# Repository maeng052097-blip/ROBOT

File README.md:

# Recycling Waste Detection Robot

재활용 쓰레기를 자동으로 인식하고 분류하는 자율주행 로봇 프로젝트

## 프로젝트 개요

카메라와 LiDAR를 활용하여 재활용 쓰레기(비닐, 스티로폼, 유리병, 종이류, 캔류, 페트병, 플라스틱류)를 실시간으로 인식하고, 물체까지의 거리를 측정하는 시스템입니다.

최종 목표는 노트북(HP VICTUS 15, RTX 4060)에서 직접 실행하여 자율주행 로봇으로 운용하는 것입니다.

## 시스템 구성

| 장비 | 용도 |
|------|------|
| HP VICTUS 15 (RTX 4060, 8GB VRAM) | 모델 학습·검증 + 실행(최종 배포 타겟) |
| Logitech StreamCam x2 | 물체 인식 카메라 |
| YDLIDAR X2 | 2D 거리 측정 (360°, 8m) |

## 인식 가능한 쓰레기 분류 (7개 클래스)

| 클래스 | 영문명 | 학습 데이터 |
|--------|--------|-----------|
| 비닐 | vinyl | 800장 |
| 스티로폼 | styrofoam | 800장 |
| 유리병 | glass_bottle | 800장 |
| 종이류 | paper | 800장 |
| 캔류 | can | 800장 |
| 페트병 | pet_bottle | 800장 |
| 플라스틱류 | plastic | 800장 |

## 학습 결과

- **모델:** YOLOv8n (nano)
- **데이터:** AIHUB 생활 폐기물 이미지 5,600장 (train 4,480 / val 1,120)
- **학습 환경:** NVIDIA RTX 4060 Laptop GPU (8GB VRAM)

| 지표 | 값 |
|------|-----|
| mAP@0.5 | 0.756 |
| mAP@0.5:0.95 | 0.665 |
| 추론 속도 (GPU) | 1.3ms/장 |

### 클래스별 성능 (AP@0.5)

| 클래스 | AP |
|--------|------|
| 스티로폼 | 0.923 |
| 캔류 | 0.759 |
| 비닐 | 0.759 |
| 페트병 | 0.745 |
| 종이류 | 0.739 |
| 플라스틱류 | 0.707 |
| 유리병 | 0.658 |

## 프로젝트 구조

```
ddd/
├── common/                      # 공용 모듈
│   ├── config.py                #   포트·임계값·경로 중앙 설정
│   ├── classes.py               #   재활용 7개 클래스 정의
│   ├── safety.py                #   LiDAR 전방 안전판단(SAFE/SLOW/DANGER)
│   ├── fusion.py                #   카메라 베어링 + LiDAR 거리 융합
│   └── camera.py                #   카메라 빠른 열기(DSHOW) + 16:9
├── config/
│   └── data.yaml                # YOLO 학습 설정
├── data/scripts/                # 데이터 변환·검증
│   ├── convert_aihub_to_yolo_v3.py
│   └── verify_labels.py
├── drivers/
│   └── LidarX2.py               # YDLIDAR X2 드라이버
├── inference/
│   └── detector.py              # YOLO 목표 탐지(좌/중/우 방향)
├── models/weights/best.pt       # 학습 가중치 (직접 배치, git 제외)
├── tests/                       # 하드웨어 스모크 테스트 + 단위 테스트
│   ├── check_devices.py         #   Arduino/LiDAR/웹캠 연결 점검
│   ├── find_camera.py           #   카메라 인덱스 찾기(내장캠 vs Logitech)
│   ├── find_front.py            #   전방각(FORWARD_ANGLE_DEG) 찾기
│   ├── test_scan.py             #   LiDAR 전방거리·안전상태(텍스트)
│   ├── test_lidar_parser.py     #   LiDAR 패킷 파서 단위테스트(HW 불필요)
│   ├── test_fusion.py           #   카메라+LiDAR 물체거리 융합 테스트
│   └── webcam_test.py           #   웹캠 + YOLO 탐지
├── visualization/
│   ├── realtime_radar.py        #   LiDAR 실시간 레이더(극좌표) 시각화
│   └── realtime_view.py         #   카메라 + LiDAR 통합 뷰
├── urt/                         # 통합 주행 + 모터
│   ├── 웹캠_LiDAR_주행제어.py     #   통합 주행 컨트롤러
│   ├── 모터2개_시리얼테스트.py    #   모터 수동 테스트(w/a/d/s)
│   ├── motor_serial.py          #   시리얼 전송 헬퍼
│   └── arduino_motor/           #   Arduino 펌웨어(PlatformIO)
└── requirements.txt
```

## 설치 및 실행

### 1. 환경 설정

```bash
# Python 3.13 가상환경 생성
python -m venv recycling_env

# 활성화 (Windows)
recycling_env\Scripts\activate

# PyTorch 설치 (CUDA 12.x)
pip install torch torchvision torchaudio --index-url https://download.pytorch.org/whl/cu124

# 나머지 패키지
pip install -r requirements.txt
```

### 2. 데이터 변환 (AIHUB → YOLO)

```bash
# AIHUB 생활 폐기물 이미지 데이터셋 필요
# https://aihub.or.kr/ (dataSetSn=140)
python data/scripts/convert_aihub_to_yolo_v3.py
```

### 3. 모델 학습

```bash
python -c "
from ultralytics import YOLO
model = YOLO('yolov8n.pt')
model.train(data='config/data.yaml', epochs=100, imgsz=640, batch=16, device=0)
"
```

### 4. LiDAR 테스트

```bash
python tests/test_scan.py
```

### 5. 하드웨어 브링업 / 통합 주행

VSCode 에서 `ddd` 폴더를 열면 Run and Debug(F5) 에 실행 구성이 준비돼 있다. 터미널로도 가능:

```bash
python tests/check_devices.py        # Arduino/LiDAR/웹캠 연결 점검
python urt/모터2개_시리얼테스트.py    # 모터 2개 수동 구동 (w/a/d/s)
python tests/webcam_test.py          # 웹캠 + YOLO 탐지/방향
python urt/웹캠_LiDAR_주행제어.py     # 통합 주행 (웹캠+LiDAR+Arduino)
```

- 학습 가중치 `best.pt` 는 `models/weights/best.pt` 에 둔다(git 제외).
- 포트/임계값은 `common/config.py` 에서 관리. LiDAR 없이 시험하려면 `REQUIRE_LIDAR=False`.
- Arduino 펌웨어는 PlatformIO 로 `urt/arduino_motor` 를 업로드.

## 진행 상황

- [x] 하드웨어 개별 테스트 (카메라, LiDAR, 모터)
- [x] 개발 환경 구축 (PyTorch + CUDA)
- [x] AIHUB 데이터 → YOLO 변환 / YOLOv8n 학습 (mAP@0.5 = 0.756)
- [x] 코드 통합: 공통 설정 · LiDAR 드라이버 · YOLO 탐지 · 모터 제어 연결
- [x] 통합 주행 컨트롤러 (웹캠 방향 + LiDAR 안전 SAFE/SLOW/DANGER + Arduino)
- [x] 하드웨어 브링업 스모크 테스트 (장치점검 / LiDAR / 웹캠)
- [ ] 실하드웨어 통합 주행 검증 및 임계값 튜닝
- [ ] 추가 데이터로 재학습 (정확도 향상)
- [ ] 노트북 실시간 추론 최적화 (TensorRT/FP16, 선택)

## 데이터셋 출처

- [AIHUB 생활 폐기물 이미지](https://aihub.or.kr/aihubdata/data/view.do?currMenu=115&topMenu=100&dataSetSn=140)
- 라벨과 이미지 배치 불일치로 인해 ZIP 카테고리 기반 자동 바운딩박스 생성 방식 사용

## 기술 스택

- **물체 인식:** YOLOv8 (ultralytics)
- **거리 측정:** YDLIDAR X2 (커스텀 드라이버)
- **카메라:** OpenCV + Logitech StreamCam
- **학습 GPU:** NVIDIA RTX 4060 Laptop (8GB VRAM)
- **실행 환경:** 노트북 (HP VICTUS 15, RTX 4060) — ultralytics + CUDA 직접 실행

## 라이선스

MIT License

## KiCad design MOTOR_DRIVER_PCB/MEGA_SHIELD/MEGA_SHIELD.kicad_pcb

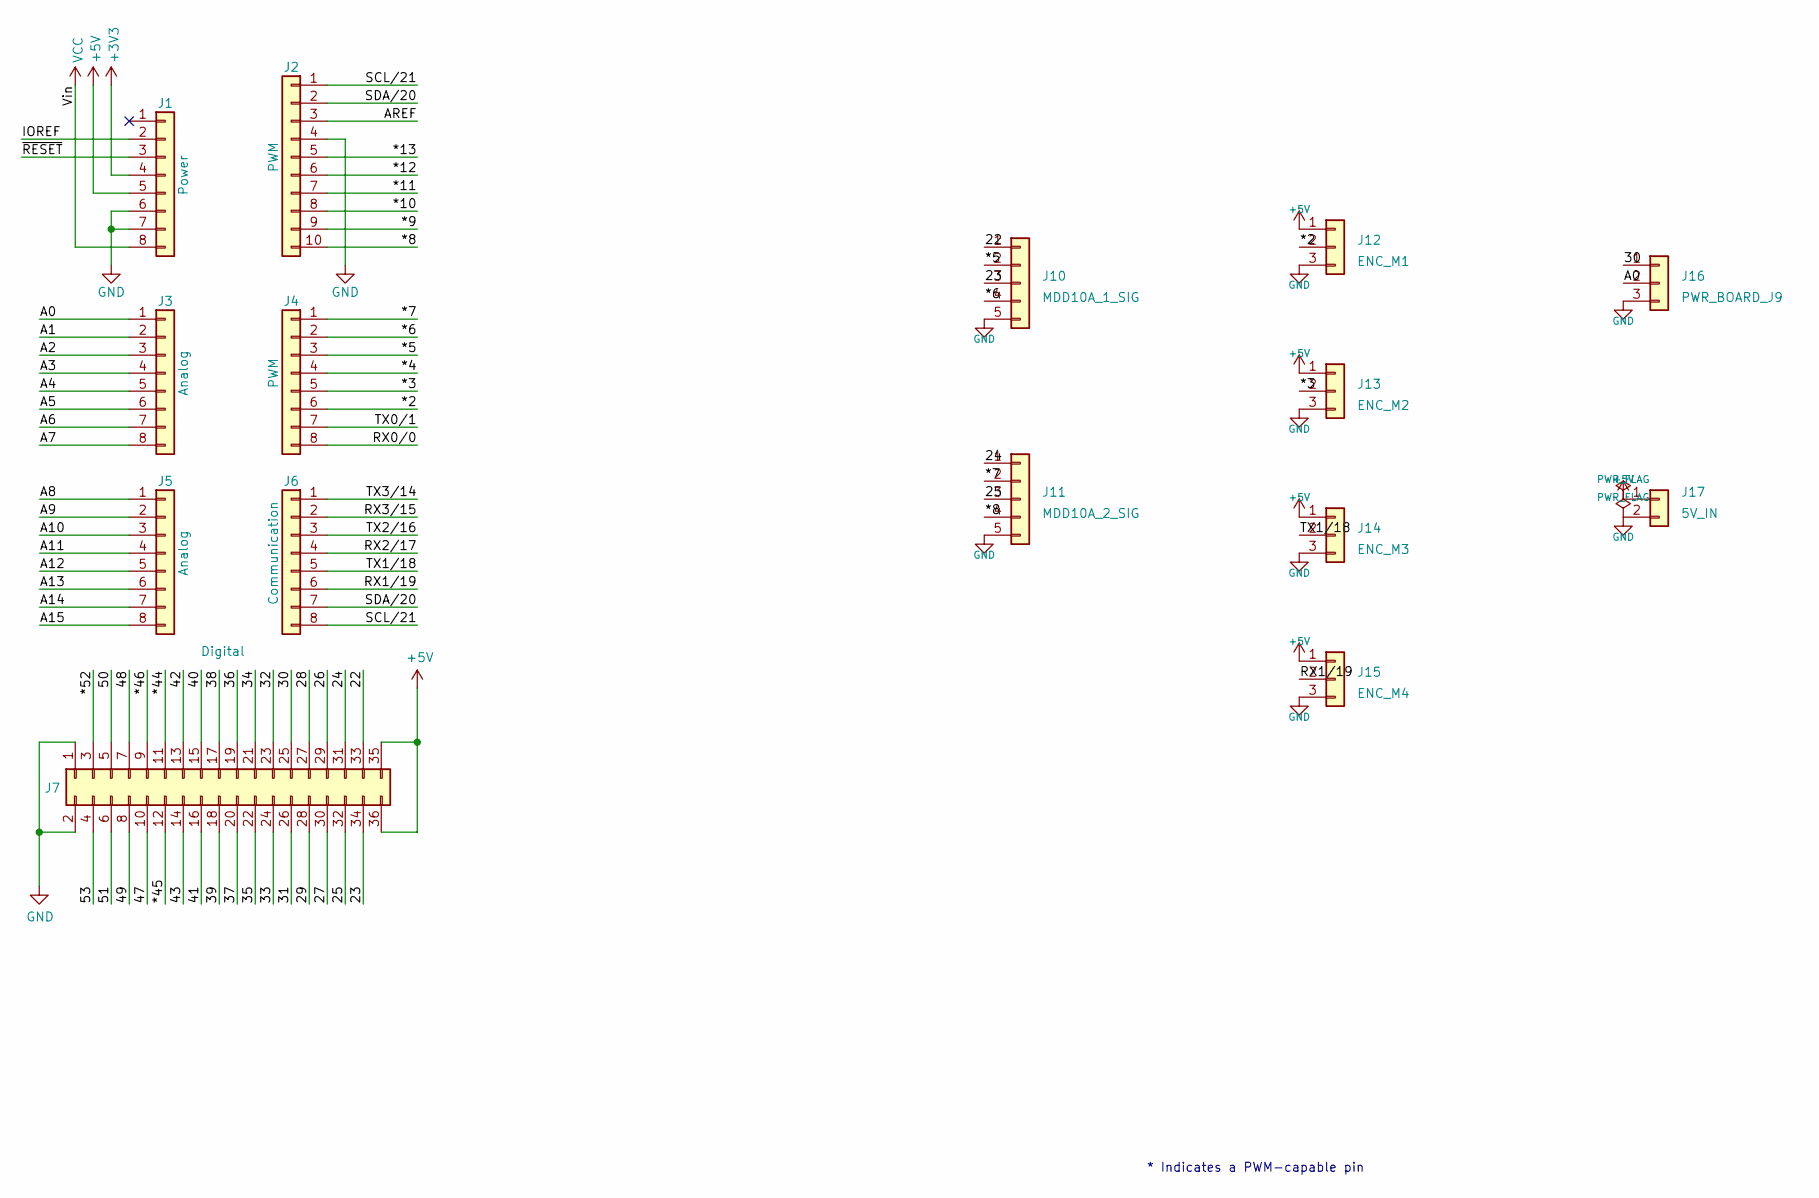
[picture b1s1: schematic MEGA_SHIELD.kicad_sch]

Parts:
J1: Power; PinSocket_1x08_P2.54mm_Vertical
J2: PWM; PinSocket_1x10_P2.54mm_Vertical
J3, J5: Analog; PinSocket_1x08_P2.54mm_Vertical
J4: PWM; PinSocket_1x08_P2.54mm_Vertical
J6: Communication; PinSocket_1x08_P2.54mm_Vertical
J7: Digital; PinSocket_2x18_P2.54mm_Vertical
J10: MDD10A_1_SIG; JST_XH_B5B-XH-A_1x05_P2.50mm_Vertical
J11: MDD10A_2_SIG; JST_XH_B5B-XH-A_1x05_P2.50mm_Vertical
J12: ENC_M1; JST_XH_B3B-XH-A_1x03_P2.50mm_Vertical
J13: ENC_M2; JST_XH_B3B-XH-A_1x03_P2.50mm_Vertical
J14: ENC_M3; JST_XH_B3B-XH-A_1x03_P2.50mm_Vertical
J15: ENC_M4; JST_XH_B3B-XH-A_1x03_P2.50mm_Vertical
J16: PWR_BOARD_J9; JST_XH_B3B-XH-A_1x03_P2.50mm_Vertical
J17: 5V_IN; JST_XH_B2B-XH-A_1x02_P2.50mm_Vertical

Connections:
+3V3: J1.4
+5V: J1.5, J7.35, J7.36, J12.1, J13.1, J14.1, J15.1, J17.1
/22: J7.33, J10.1
/23: J7.34, J10.3
/24: J7.31, J11.1
/25: J7.32, J11.3
/26: J7.29
/27: J7.30
/28: J7.27
/29: J7.28
/30: J7.25, J16.1
/31: J7.26
/32: J7.23
/33: J7.24
/34: J7.21
/35: J7.22
/36: J7.19
/37: J7.20
/38: J7.17
/39: J7.18
/40: J7.15
/41: J7.16
/42: J7.13
/43: J7.14
/47: J7.10
/48: J7.7
/49: J7.8
/50: J7.5
/51: J7.6
/53: J7.4
/*2: J4.6, J12.2
/*3: J4.5, J13.2
/*4: J4.4
/*5: J4.3, J10.2
/*6: J4.2, J10.4
/*7: J4.1, J11.2
/*8: J2.10, J11.4
/*9: J2.9
/*10: J2.8
/*11: J2.7
/*12: J2.6
/*13: J2.5
/*44: J7.11
/*45: J7.12
/*46: J7.9
/*52: J7.3
/A0: J3.1, J16.2
/A1: J3.2
/A2: J3.3
/A3: J3.4
/A4: J3.5
/A5: J3.6
/A6: J3.7
/A7: J3.8
/A8: J5.1
/A9: J5.2
/A10: J5.3
/A11: J5.4
/A12: J5.5
/A13: J5.6
/A14: J5.7
/A15: J5.8
/AREF: J2.3
/IOREF: J1.2
/RX0/0: J4.8
/RX1/19: J6.6, J15.2
/RX2/17: J6.4
/RX3/15: J6.2
/SCL/21: J2.1, J6.8
/SDA/20: J2.2, J6.7
/TX0/1: J4.7
/TX1/18: J6.5, J14.2
/TX2/16: J6.3
/TX3/14: J6.1
/~RESET: J1.3
GND: J1.6, J1.7, J2.4, J7.1, J7.2, J10.5, J11.5, J12.3, J13.3, J14.3, J15.3, J16.3, J17.2
VCC: J1.8

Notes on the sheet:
* Indicates a PWM-capable pin

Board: 2 copper layers, 21 parts (0 on the bottom side), 18 nets, no tracks yet.

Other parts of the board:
MH1, MH2, MH3, MH4, MH5, MH6: MountingHole_3.2mm

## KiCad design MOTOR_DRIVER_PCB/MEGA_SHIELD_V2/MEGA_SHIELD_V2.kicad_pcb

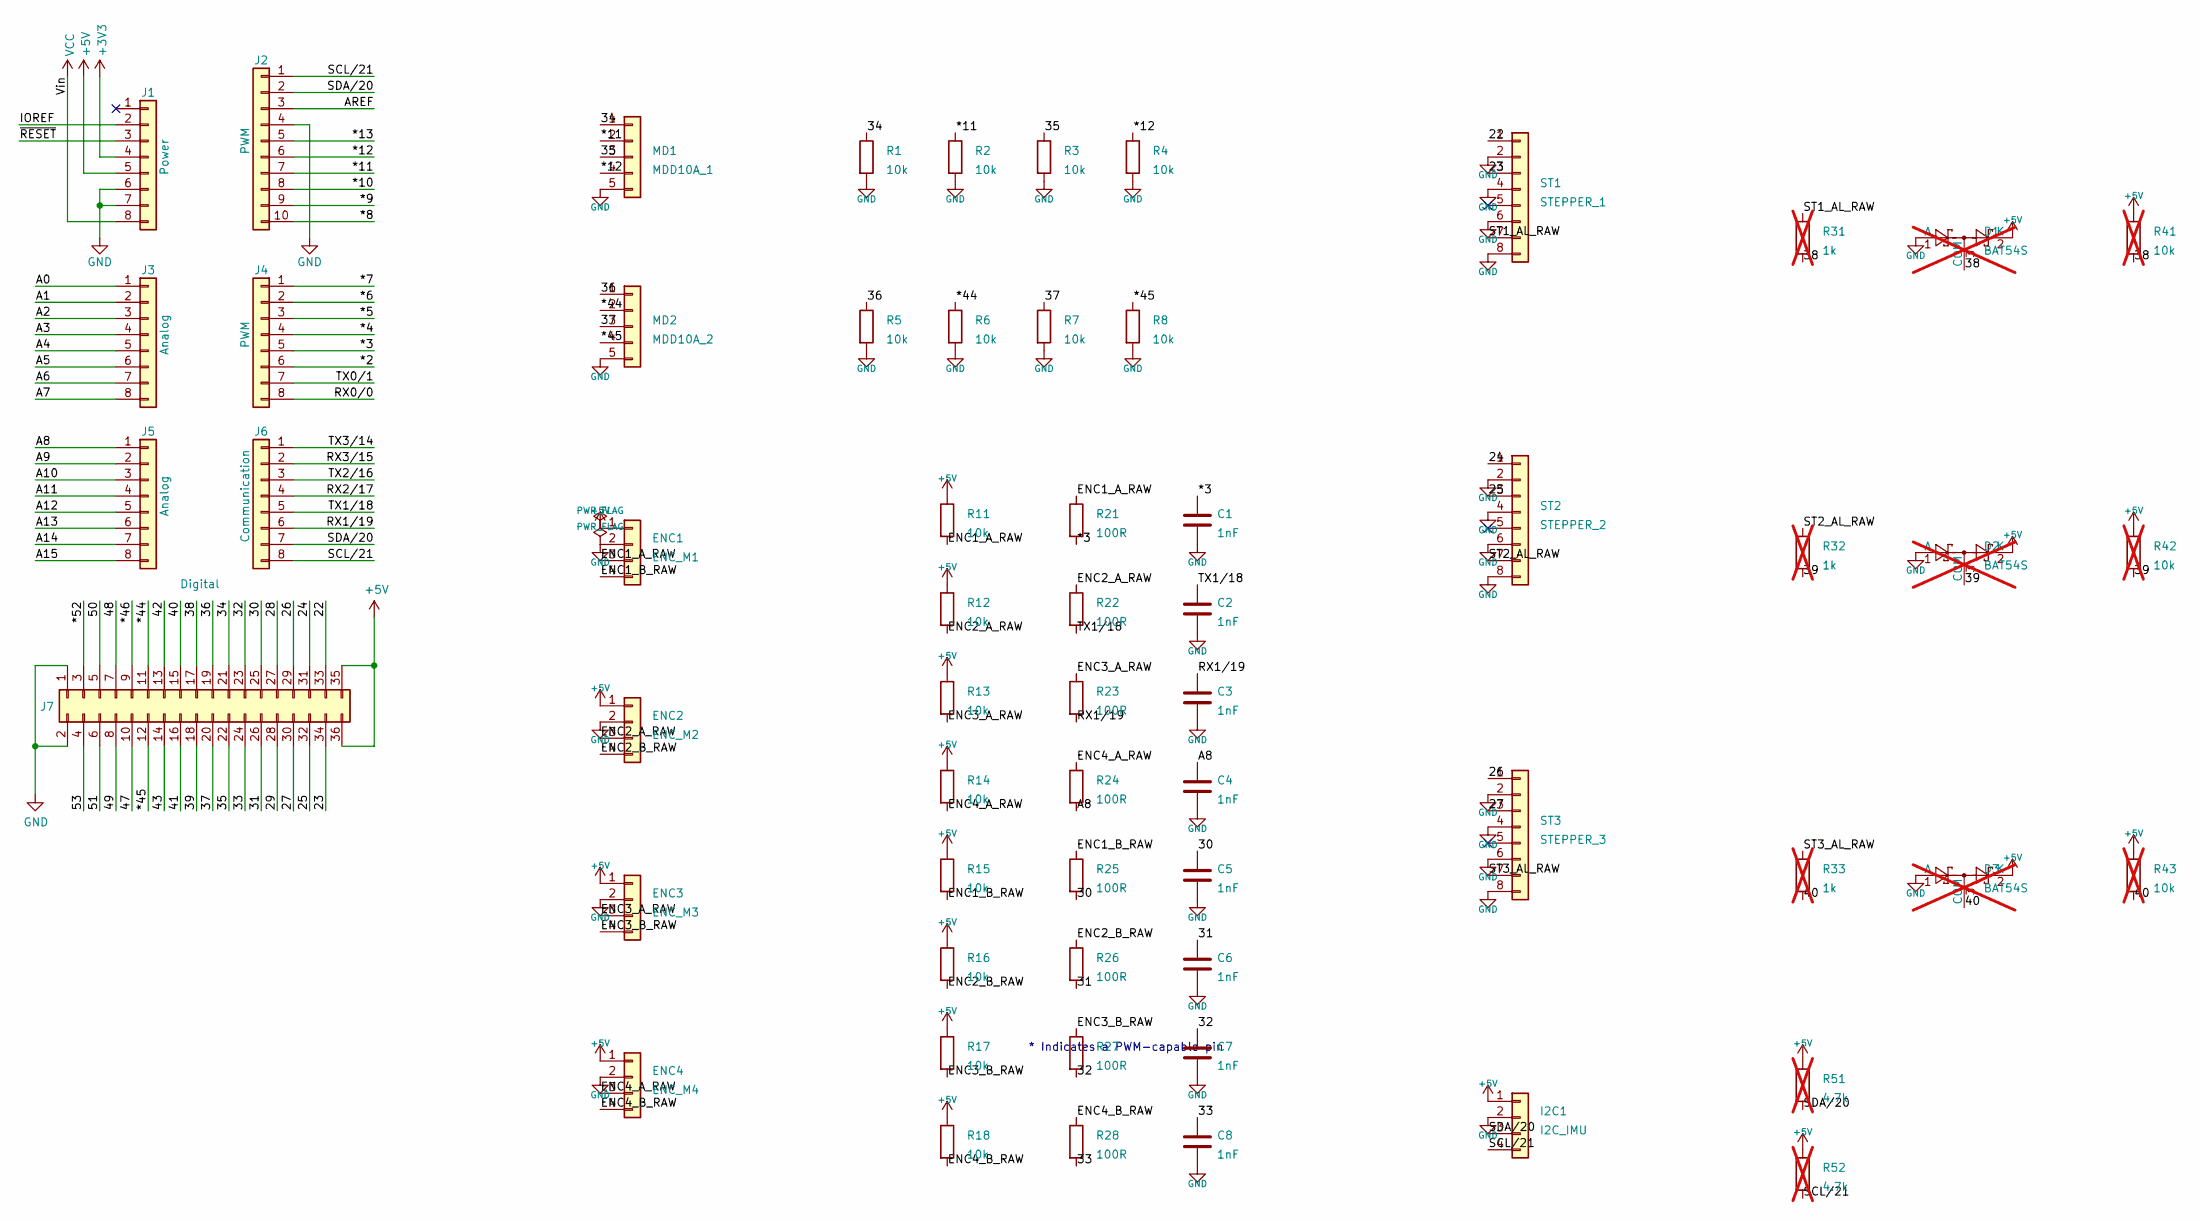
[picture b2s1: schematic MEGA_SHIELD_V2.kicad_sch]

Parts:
C1, C2, C3, C4, C5, C6, C7, C8: 1nF; C_0805_2012Metric
D1, D2, D3: BAT54S; SOT-23; not fitted
ENC1: ENC_M1; Molex_KK-254_AE-6410-04A_1x04_P2.54mm_Vertical
ENC2: ENC_M2; Molex_KK-254_AE-6410-04A_1x04_P2.54mm_Vertical
ENC3: ENC_M3; Molex_KK-254_AE-6410-04A_1x04_P2.54mm_Vertical
ENC4: ENC_M4; Molex_KK-254_AE-6410-04A_1x04_P2.54mm_Vertical
I2C1: I2C_IMU; Molex_KK-254_AE-6410-04A_1x04_P2.54mm_Vertical
J1: Power; PinSocket_1x08_P2.54mm_Vertical
J2: PWM; PinSocket_1x10_P2.54mm_Vertical
J3, J5: Analog; PinSocket_1x08_P2.54mm_Vertical
J4: PWM; PinSocket_1x08_P2.54mm_Vertical
J6: Communication; PinSocket_1x08_P2.54mm_Vertical
J7: Digital; PinSocket_2x18_P2.54mm_Vertical
MD1: MDD10A_1; Molex_KK-254_AE-6410-05A_1x05_P2.54mm_Vertical
MD2: MDD10A_2; Molex_KK-254_AE-6410-05A_1x05_P2.54mm_Vertical
R1, R2, R3, R4, R5, R6, R7, R8, R11, R12, R13, R14, R15, R16, R17, R18: 10k; R_0805_2012Metric
R21, R22, R23, R24, R25, R26, R27, R28: 100R; R_0805_2012Metric
R31, R32, R33: 1k; R_0805_2012Metric; not fitted
R41, R42, R43: 10k; R_0805_2012Metric; not fitted
R51, R52: 4.7k; R_0805_2012Metric; not fitted
ST1: STEPPER_1; Molex_KK-254_AE-6410-08A_1x08_P2.54mm_Vertical
ST2: STEPPER_2; Molex_KK-254_AE-6410-08A_1x08_P2.54mm_Vertical
ST3: STEPPER_3; Molex_KK-254_AE-6410-08A_1x08_P2.54mm_Vertical

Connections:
+3V3: J1.4
+5V: D1.2 (K), D2.2 (K), D3.2 (K), ENC1.1, ENC2.1, ENC3.1, ENC4.1, I2C1.1, J1.5, J7.35, J7.36, R11.1, R12.1, R13.1, R14.1, R15.1, R16.1, R17.1, R18.1, R41.1, R42.1, R43.1, R51.1, R52.1
/22: J7.33, ST1.1
/23: J7.34, ST1.3
/24: J7.31, ST2.1
/25: J7.32, ST2.3
/26: J7.29, ST3.1
/27: J7.30, ST3.3
/28: J7.27
/29: J7.28
/30: C5.1, J7.25, R25.2
/31: C6.1, J7.26, R26.2
/32: C7.1, J7.23, R27.2
/33: C8.1, J7.24, R28.2
/34: J7.21, MD1.1, R1.1
/35: J7.22, MD1.3, R3.1
/36: J7.19, MD2.1, R5.1
/37: J7.20, MD2.3, R7.1
/38: D1.3 (COM), J7.17, R31.2, R41.2
/39: D2.3 (COM), J7.18, R32.2, R42.2
/40: D3.3 (COM), J7.15, R33.2, R43.2
/41: J7.16
/42: J7.13
/43: J7.14
/47: J7.10
/48: J7.7
/49: J7.8
/50: J7.5
/51: J7.6
/53: J7.4
/*2: J4.6
/*3: C1.1, J4.5, R21.2
/*4: J4.4
/*5: J4.3
/*6: J4.2
/*7: J4.1
/*8: J2.10
/*9: J2.9
/*10: J2.8
/*11: J2.7, MD1.2, R2.1
/*12: J2.6, MD1.4, R4.1
/*13: J2.5
/*44: J7.11, MD2.2, R6.1
/*45: J7.12, MD2.4, R8.1
/*46: J7.9
/*52: J7.3
/A0: J3.1
/A1: J3.2
/A2: J3.3
/A3: J3.4
/A4: J3.5
/A5: J3.6
/A6: J3.7
/A7: J3.8
/A8: C4.1, J5.1, R24.2
/A9: J5.2
/A10: J5.3
/A11: J5.4
/A12: J5.5
/A13: J5.6
/A14: J5.7
/A15: J5.8
/AREF: J2.3
/ENC1_A_RAW: ENC1.3, R11.2, R21.1
/ENC1_B_RAW: ENC1.4, R15.2, R25.1
/ENC2_A_RAW: ENC2.3, R12.2, R22.1
/ENC2_B_RAW: ENC2.4, R16.2, R26.1
/ENC3_A_RAW: ENC3.3, R13.2, R23.1
/ENC3_B_RAW: ENC3.4, R17.2, R27.1
/ENC4_A_RAW: ENC4.3, R14.2, R24.1
/ENC4_B_RAW: ENC4.4, R18.2, R28.1
/IOREF: J1.2
/RX0/0: J4.8
/RX1/19: C3.1, J6.6, R23.2
/RX2/17: J6.4
/RX3/15: J6.2
/SCL/21: I2C1.4, J2.1, J6.8, R52.2
/SDA/20: I2C1.3, J2.2, J6.7, R51.2
/ST1_AL_RAW: R31.1, ST1.7
/ST2_AL_RAW: R32.1, ST2.7
/ST3_AL_RAW: R33.1, ST3.7
/TX0/1: J4.7
/TX1/18: C2.1, J6.5, R22.2
/TX2/16: J6.3
/TX3/14: J6.1
/~RESET: J1.3
GND: C1.2, C2.2, C3.2, C4.2, C5.2, C6.2, C7.2, C8.2, D1.1 (A), D2.1 (A), D3.1 (A), ENC1.2, ENC2.2, ENC3.2, ENC4.2, I2C1.2, J1.6, J1.7, J2.4, J7.1, J7.2, MD1.5, MD2.5, R1.2, R2.2, R3.2, R4.2, R5.2, R6.2, R7.2, R8.2, ST1.2, ST1.4, ST1.6, ST1.8, ST2.2, ST2.4, ST2.6, ST2.8, ST3.2, ST3.4, ST3.6, ST3.8
VCC: J1.8

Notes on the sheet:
* Indicates a PWM-capable pin

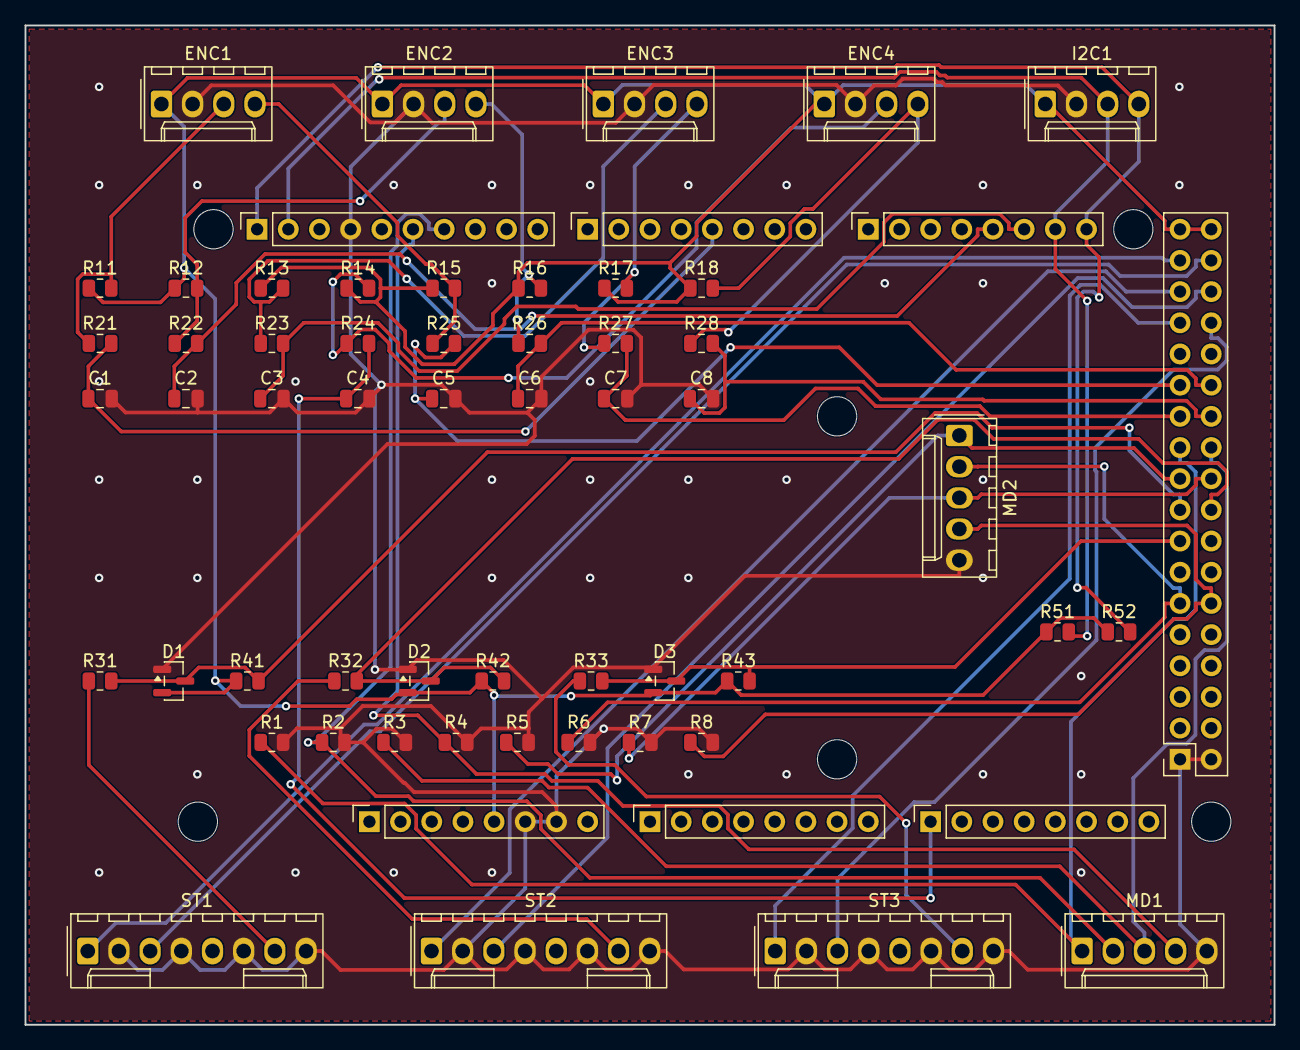
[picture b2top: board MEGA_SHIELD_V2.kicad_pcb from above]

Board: 2 copper layers, 101.8 x 81.4 mm, 66 parts (0 on the bottom side), 40 nets.

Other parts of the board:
MH1, MH2, MH3, MH4, MH5, MH6: MountingHole_3.2mm

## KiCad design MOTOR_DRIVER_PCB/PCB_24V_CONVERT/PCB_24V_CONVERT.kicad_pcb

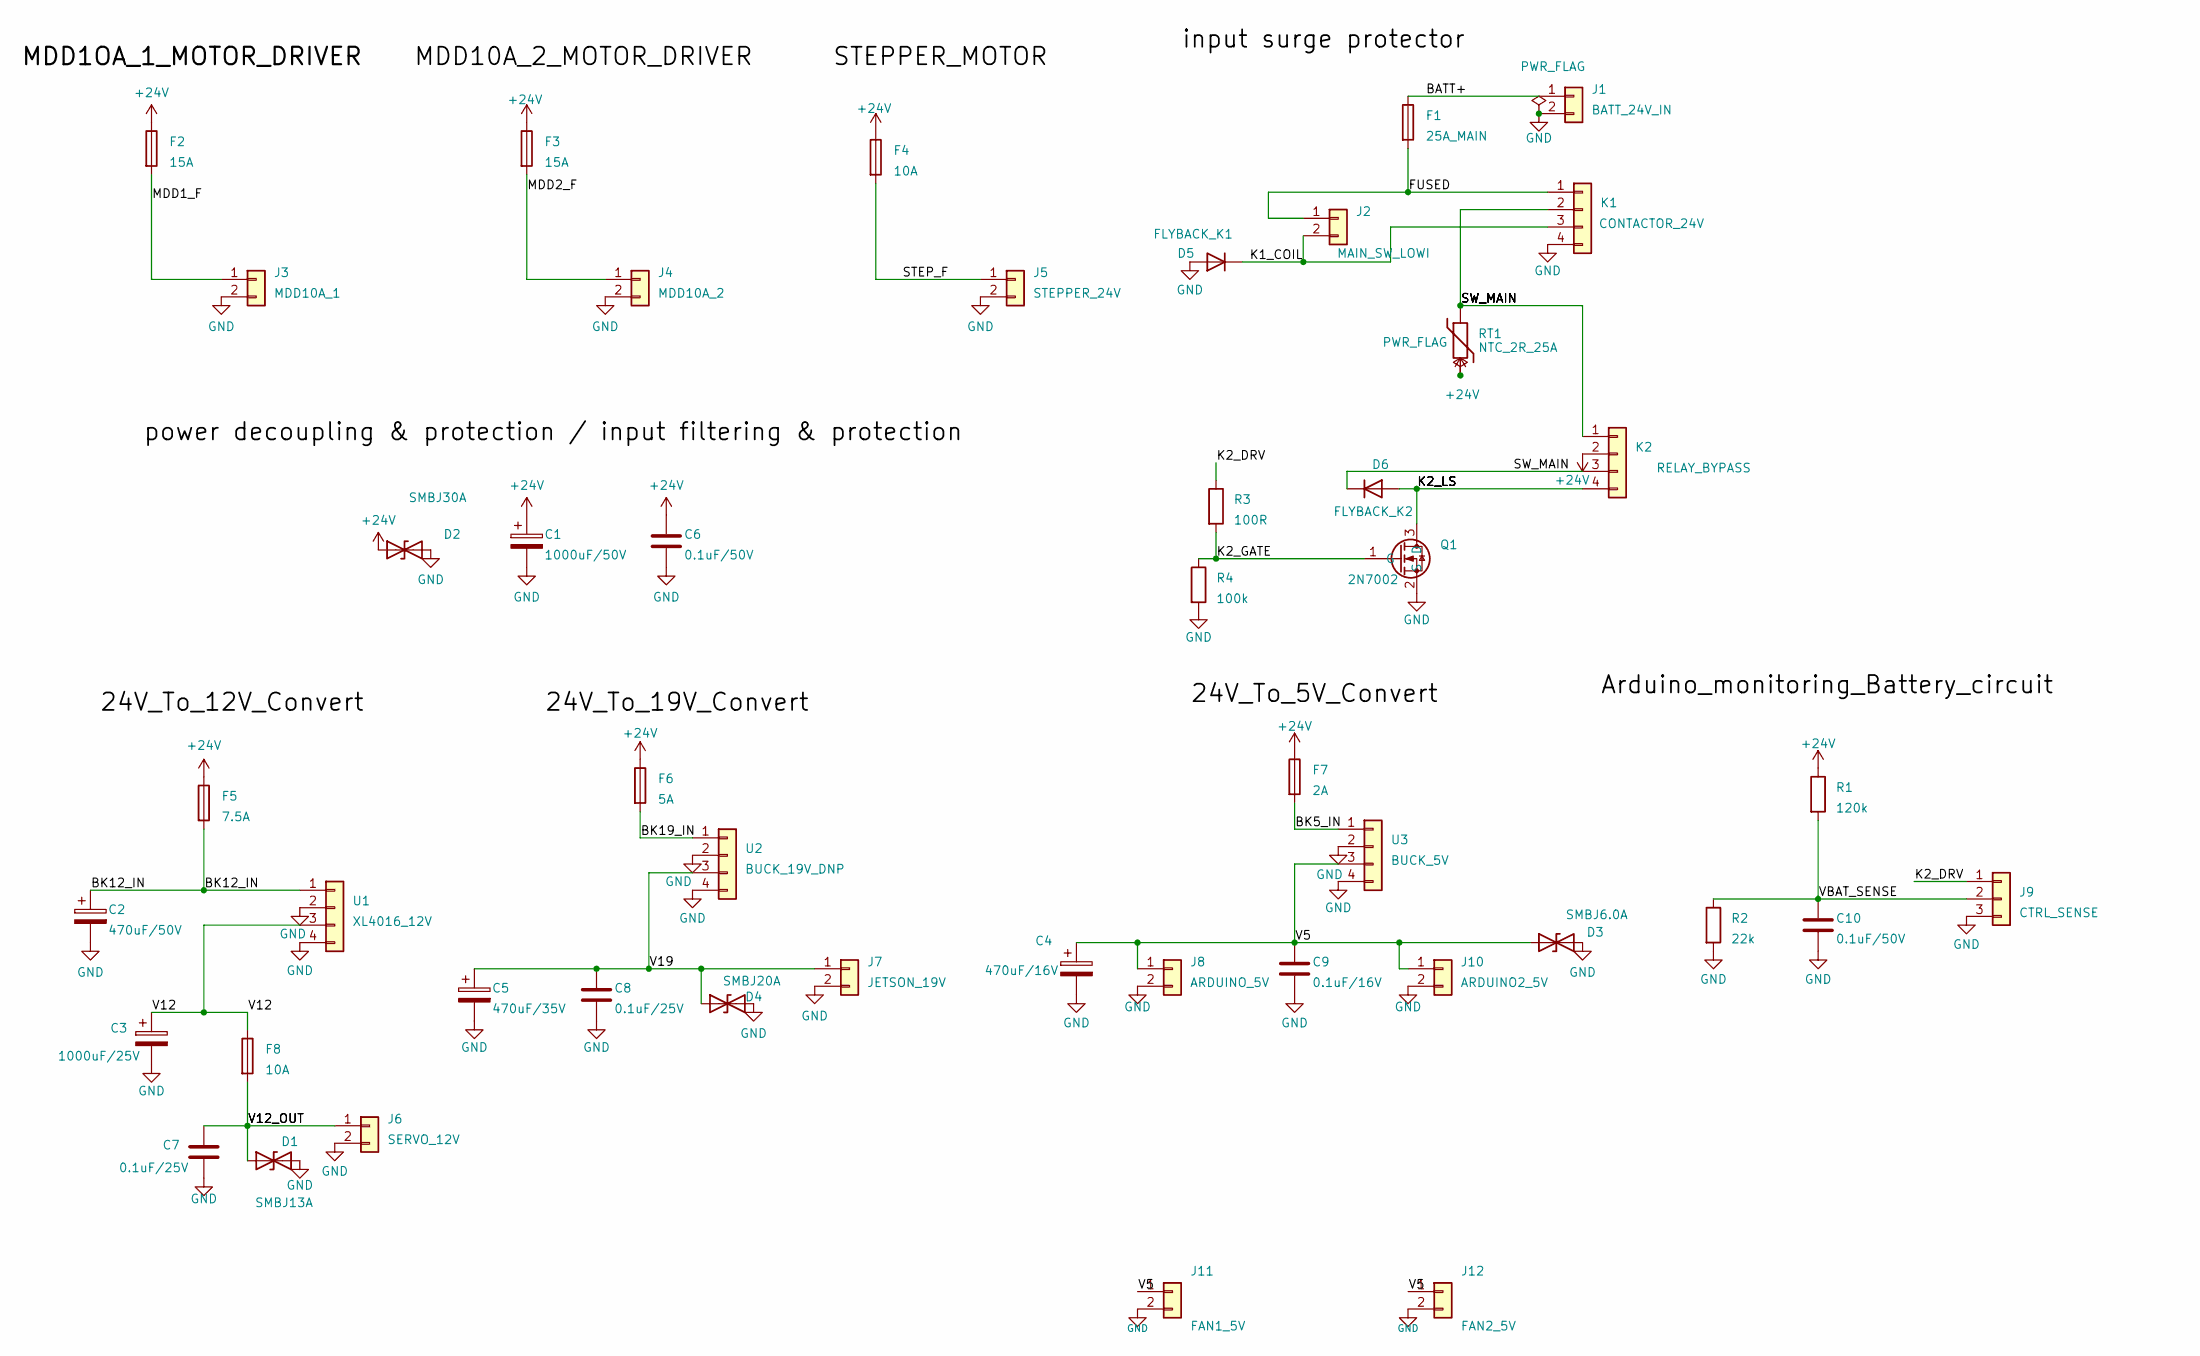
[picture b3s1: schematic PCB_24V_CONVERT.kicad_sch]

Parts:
C1: 1000uF/50V; CP_Radial_D12.5mm_P5.00mm
C2: 470uF/50V; CP_Radial_D10.0mm_P5.00mm
C3: 1000uF/25V; CP_Radial_D10.0mm_P5.00mm
C4: 470uF/16V; CP_Radial_D8.0mm_P3.50mm
C5: 470uF/35V; CP_Radial_D10.0mm_P5.00mm
C6, C10: 0.1uF/50V; C_Disc_D5.0mm_W2.5mm_P5.00mm
C7, C8: 0.1uF/25V; C_Disc_D5.0mm_W2.5mm_P5.00mm
C9: 0.1uF/16V; C_Disc_D5.0mm_W2.5mm_P5.00mm
D1: SMBJ13A; D_SMB
D2: SMBJ30A; D_SMB
D3: SMBJ6.0A; D_SMB
D4: SMBJ20A; D_SMB
D5: FLYBACK_K1; D_DO-41_SOD81_P7.62mm_Horizontal
D6: FLYBACK_K2; D_DO-41_SOD81_P7.62mm_Horizontal
F1: 25A_MAIN; FuseHolder_Blade_ATO_Littelfuse_FLR_178.6165
F2, F3: 15A; FuseHolder_Blade_ATO_Littelfuse_FLR_178.6165
F4, F8: 10A; FuseHolder_Blade_ATO_Littelfuse_FLR_178.6165
F5: 7.5A; FuseHolder_Blade_ATO_Littelfuse_FLR_178.6165
F6: 5A; FuseHolder_Blade_ATO_Littelfuse_FLR_178.6165
F7: 2A; FuseHolder_Blade_ATO_Littelfuse_FLR_178.6165
J1: BATT_24V_IN; AMASS_XT60PW-M_1x02_P7.20mm_Horizontal
J2: MAIN_SW_LOWI; TerminalBlock_Phoenix_MKDS-3-2-5.08_1x02_P5.08mm_Horizontal
J3: MDD10A_1; TerminalBlock_Phoenix_MKDS-3-2-5.08_1x02_P5.08mm_Horizontal
J4: MDD10A_2; TerminalBlock_Phoenix_MKDS-3-2-5.08_1x02_P5.08mm_Horizontal
J5: STEPPER_24V; TerminalBlock_Phoenix_MKDS-3-2-5.08_1x02_P5.08mm_Horizontal
J6: SERVO_12V; TerminalBlock_Phoenix_MKDS-3-2-5.08_1x02_P5.08mm_Horizontal
J7: JETSON_19V; TerminalBlock_Phoenix_MKDS-3-2-5.08_1x02_P5.08mm_Horizontal
J8: ARDUINO_5V; TerminalBlock_Phoenix_MKDS-3-2-5.08_1x02_P5.08mm_Horizontal
J9: CTRL_SENSE; PinHeader_1x03_P2.54mm_Vertical
J10: ARDUINO2_5V; TerminalBlock_Phoenix_MKDS-3-2-5.08_1x02_P5.08mm_Horizontal
J11: FAN1_5V; TerminalBlock_Phoenix_MKDS-3-2-5.08_1x02_P5.08mm_Horizontal
J12: FAN2_5V; TerminalBlock_Phoenix_MKDS-3-2-5.08_1x02_P5.08mm_Horizontal
K1: CONTACTOR_24V; TerminalBlock_Phoenix_MKDS-3-4-5.08_1x04_P5.08mm_Horizontal
K2: RELAY_BYPASS; TerminalBlock_Phoenix_MKDS-3-4-5.08_1x04_P5.08mm_Horizontal
Q1: 2N7002; SOT-23
R1: 120k; R_Axial_DIN0207_L6.3mm_D2.5mm_P7.62mm_Horizontal
R2: 22k; R_Axial_DIN0207_L6.3mm_D2.5mm_P7.62mm_Horizontal
R3: 100R; R_Axial_DIN0207_L6.3mm_D2.5mm_P7.62mm_Horizontal
R4: 100k; R_Axial_DIN0207_L6.3mm_D2.5mm_P7.62mm_Horizontal
RT1: NTC_2R_25A; RV_Disc_D12mm_W5.8mm_P7.5mm
U1: XL4016_12V; TerminalBlock_Phoenix_MKDS-3-4-5.08_1x04_P5.08mm_Horizontal
U2: BUCK_19V_DNP; TerminalBlock_Phoenix_MKDS-3-4-5.08_1x04_P5.08mm_Horizontal
U3: BUCK_5V; TerminalBlock_Phoenix_MKDS-3-4-5.08_1x04_P5.08mm_Horizontal

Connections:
+24V: C1.1, C6.1, D2.1 (A1), F2.1, F3.1, F4.1, F5.1, F6.1, F7.1, K2.2, R1.1, RT1.2
/BATT+: F1.1, J1.1
/BK5_IN: F7.2, U3.1
/BK12_IN: C2.1, F5.2, U1.1
/BK19_IN: F6.2, U2.1
/FUSED: F1.2, J2.1, K1.1
/K1_COIL: D5.1 (K), J2.2, K1.3
/K2_DRV: J9.1, R3.1
/K2_GATE: Q1.1 (G), R3.2, R4.1
/K2_LS: D6.2 (A), K2.4, Q1.3 (D)
/MDD1_F: F2.2, J3.1
/MDD2_F: F3.2, J4.1
/STEP_F: F4.2, J5.1
/SW_MAIN: D6.1 (K), K1.2, K2.1, K2.3, RT1.1
/V5: C4.1, C9.1, D3.1 (A1), J8.1, J10.1, J11.1, J12.1, U3.3
/V12: C3.1, F8.1, U1.3
/V12_OUT: C7.1, D1.1 (A1), F8.2, J6.1
/V19: C5.1, C8.1, D4.1 (A1), J7.1, U2.3
/VBAT_SENSE: C10.1, J9.2, R1.2, R2.1
GND: C1.2, C2.2, C3.2, C4.2, C5.2, C6.2, C7.2, C8.2, C9.2, C10.2, D1.2 (A2), D2.2 (A2), D3.2 (A2), D4.2 (A2), D5.2 (A), J1.2, J3.2, J4.2, J5.2, J6.2, J7.2, J8.2, J9.3, J10.2, J11.2, J12.2, K1.4, Q1.2 (S), R2.2, R4.2, U1.2, U1.4, U2.2, U2.4, U3.2, U3.4

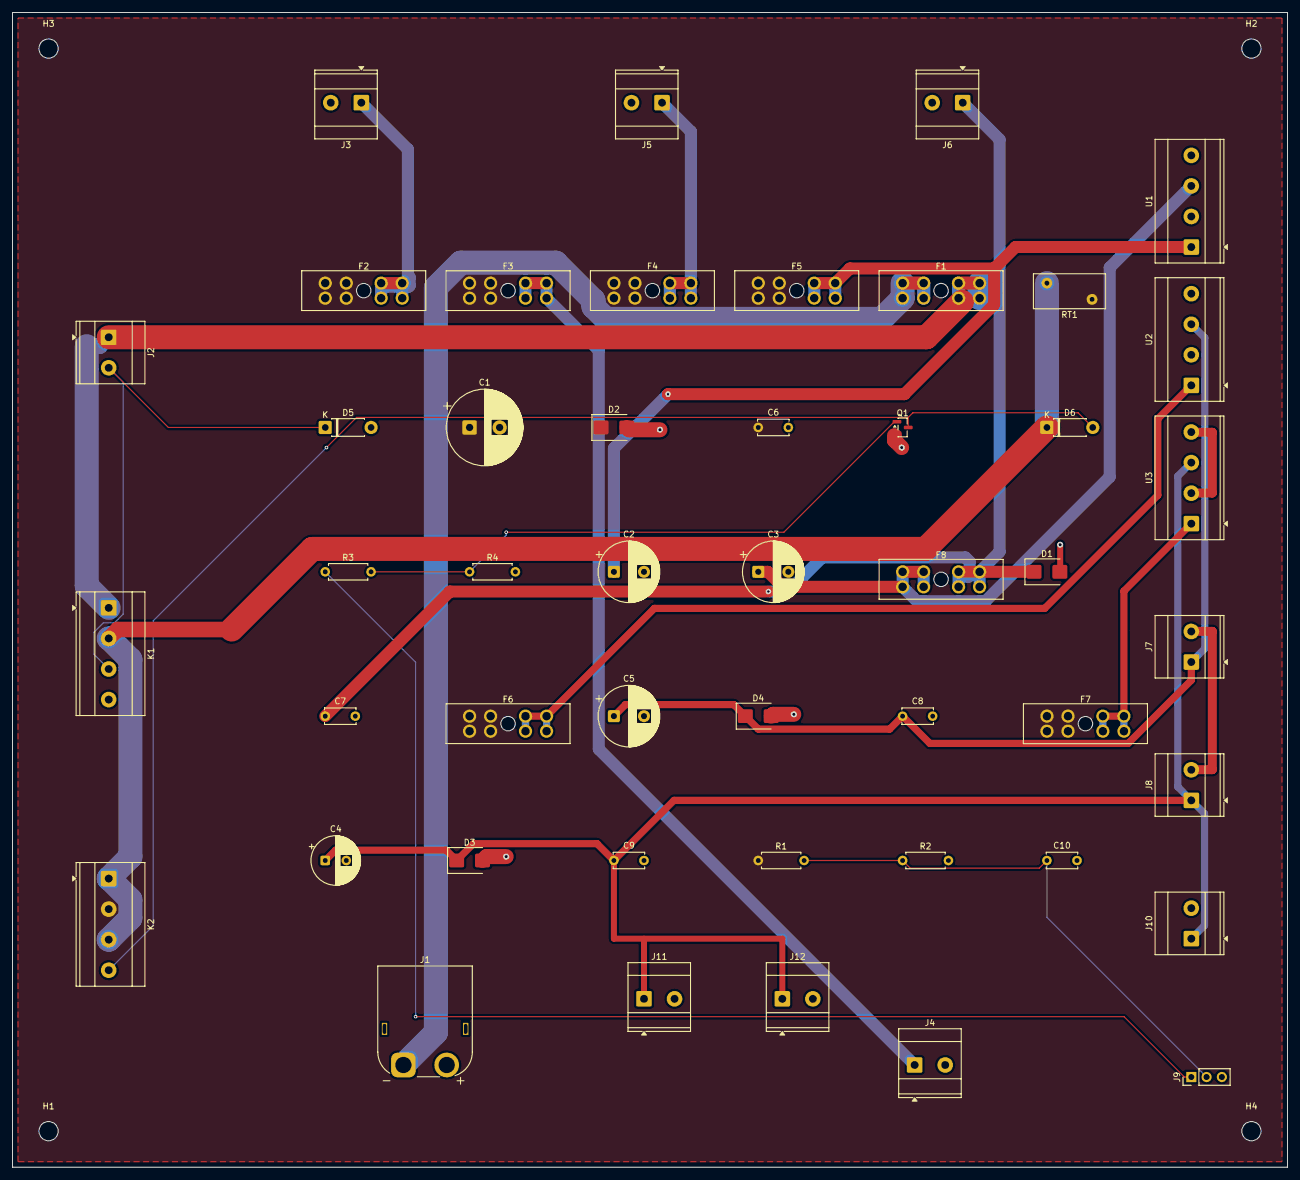
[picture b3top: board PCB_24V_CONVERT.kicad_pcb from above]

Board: 2 copper layers, 212.0 x 192.0 mm, 51 parts (0 on the bottom side), 20 nets.

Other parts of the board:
H1, H2, H3, H4: MountingHole_3.2mm_M3

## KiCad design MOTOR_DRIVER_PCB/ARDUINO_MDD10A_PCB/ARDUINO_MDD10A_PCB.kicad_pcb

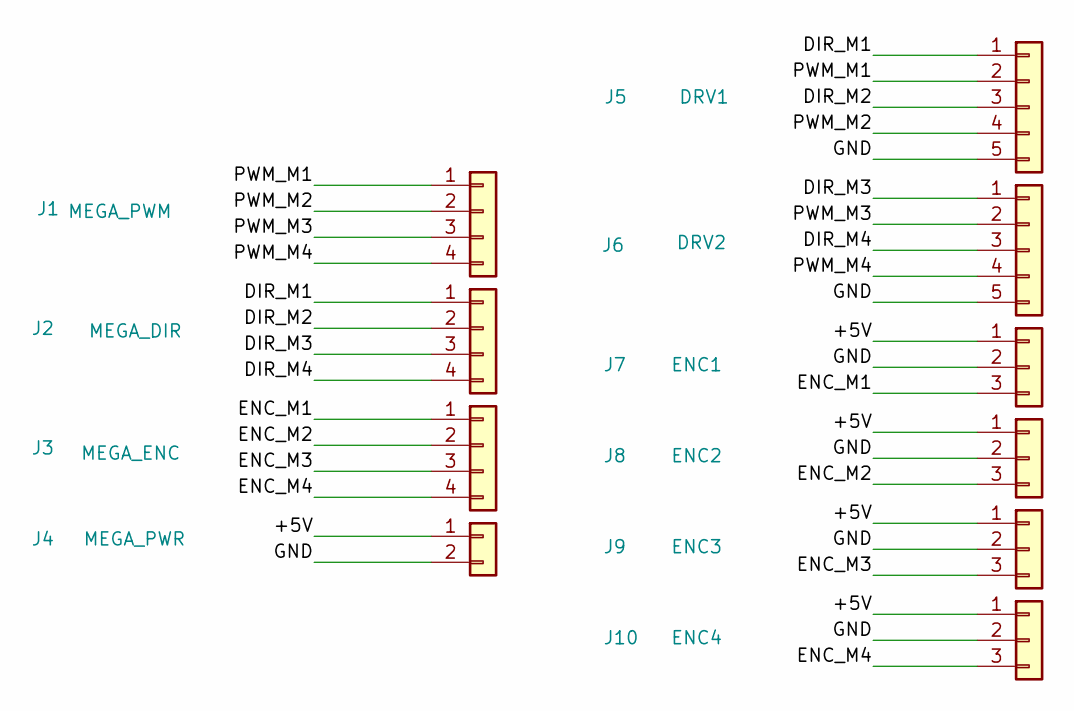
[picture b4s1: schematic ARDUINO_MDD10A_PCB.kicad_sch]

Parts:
J1: MEGA_PWM; PinHeader_1x04_P2.54mm_Vertical
J2: MEGA_DIR; PinHeader_1x04_P2.54mm_Vertical
J3: MEGA_ENC; PinHeader_1x04_P2.54mm_Vertical
J4: MEGA_PWR; PinHeader_1x02_P2.54mm_Vertical
J5: DRV1; PinHeader_1x05_P2.54mm_Vertical
J6: DRV2; PinHeader_1x05_P2.54mm_Vertical
J7: ENC1; PinHeader_1x03_P2.54mm_Vertical
J8: ENC2; PinHeader_1x03_P2.54mm_Vertical
J9: ENC3; PinHeader_1x03_P2.54mm_Vertical
J10: ENC4; PinHeader_1x03_P2.54mm_Vertical

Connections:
/+5V: J4.1, J7.1, J8.1, J9.1, J10.1
/DIR_M1: J2.1, J5.1
/DIR_M2: J2.2, J5.3
/DIR_M3: J2.3, J6.1
/DIR_M4: J2.4, J6.3
/ENC_M1: J3.1, J7.3
/ENC_M2: J3.2, J8.3
/ENC_M3: J3.3, J9.3
/ENC_M4: J3.4, J10.3
/GND: J4.2, J5.5, J6.5, J7.2, J8.2, J9.2, J10.2
/PWM_M1: J1.1, J5.2
/PWM_M2: J1.2, J5.4
/PWM_M3: J1.3, J6.2
/PWM_M4: J1.4, J6.4

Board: 2 copper layers, 10 parts (0 on the bottom side), 14 nets, no tracks yet.
